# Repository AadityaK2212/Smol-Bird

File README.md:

# Smol-Bird
It is a mini console that can run a flappy bird game using a coin cell battery and a 8X8 LED grid. i originally saw someone make a small buisness card that can play video games, so I elaborated off of that and made it to only play flappy bird. also created one for pong. It runs on an ATtiny 1616 Microcontroller. I made this because it seemed like something fun, that I could just keep on me in case I ever got bored, and it would be cool to show off. I also need these for a competition at my school Hack Club, and i am giving these away as some of the prizes. It aslo seemed like a begginer friendly project that I learned more from.

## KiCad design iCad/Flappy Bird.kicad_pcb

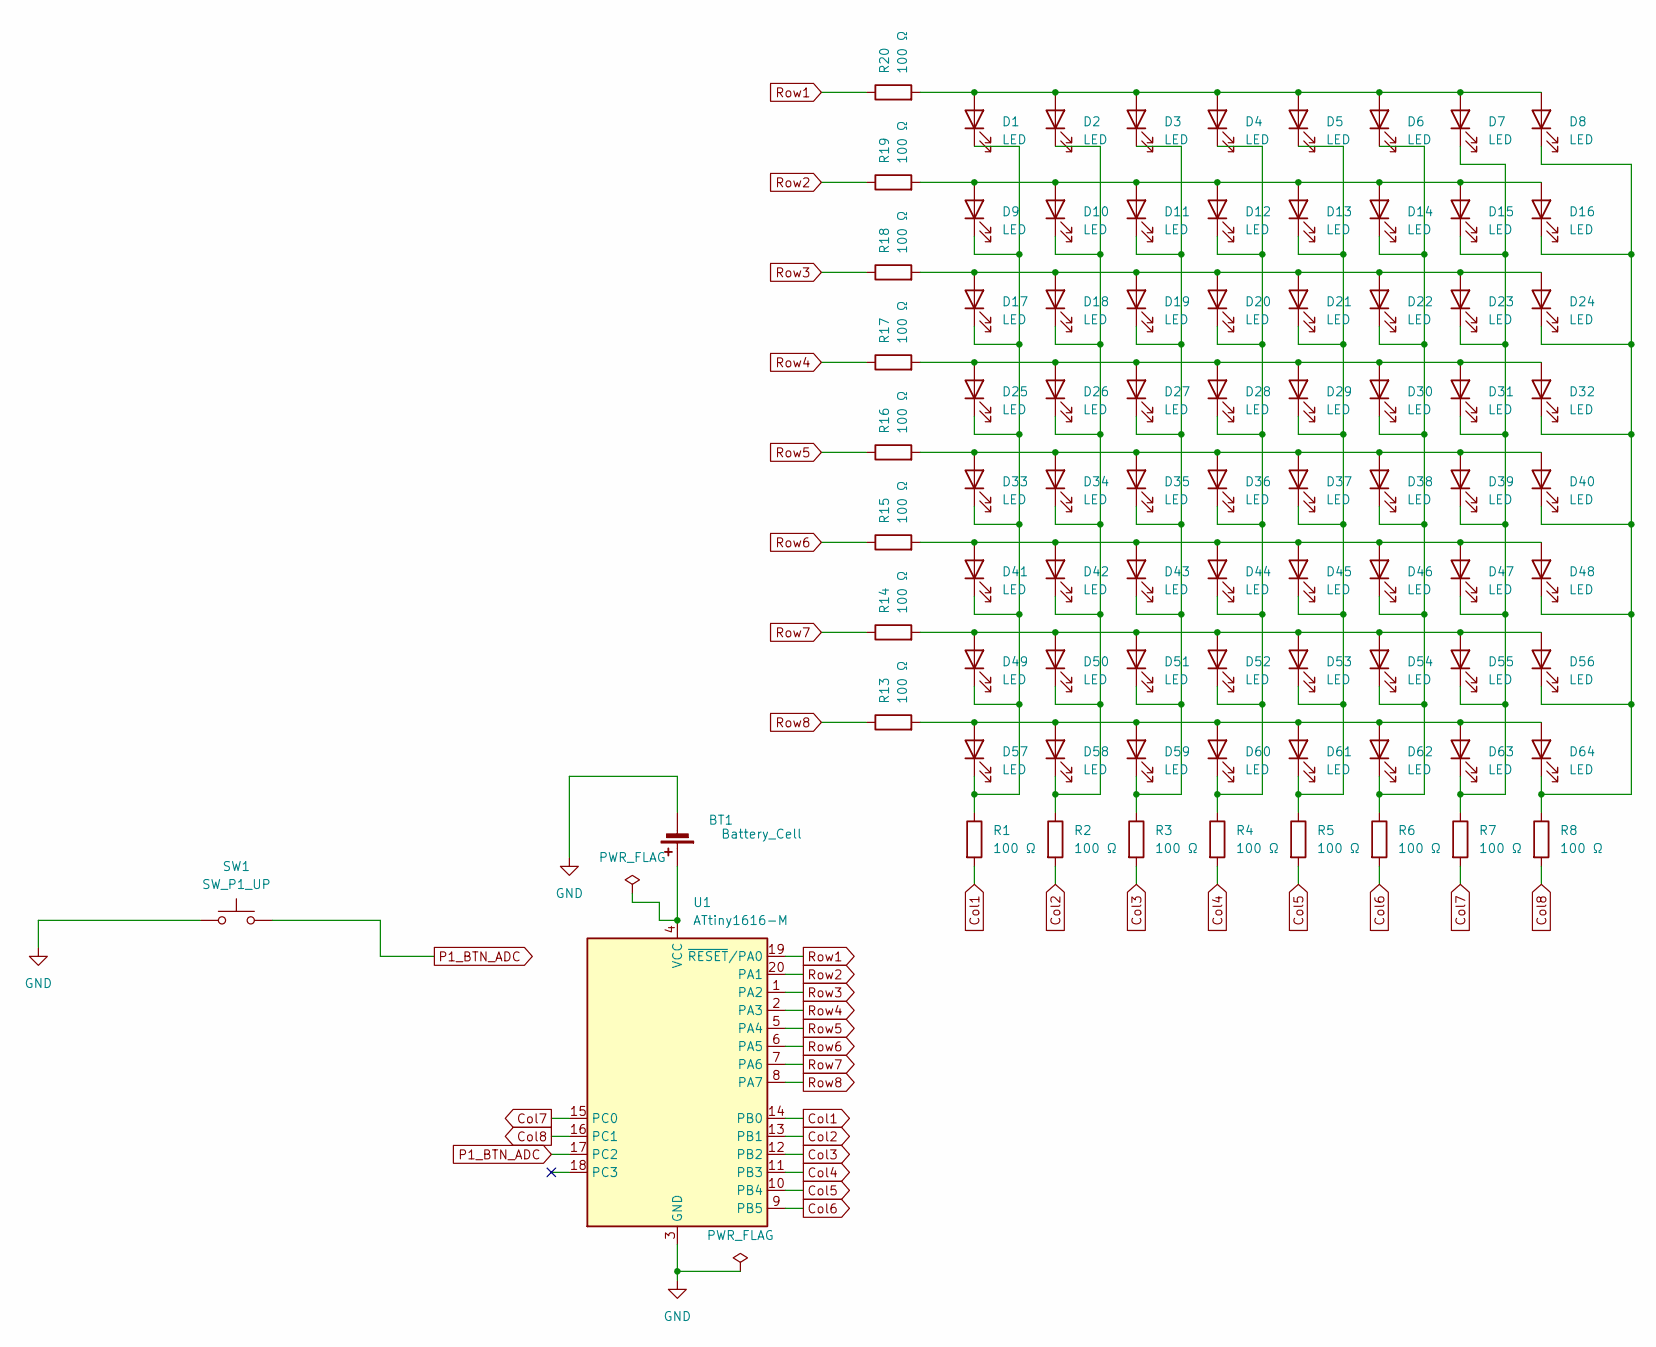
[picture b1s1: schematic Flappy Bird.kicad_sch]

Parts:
BT1: Battery_Cell; BatteryHolder_Keystone_1057_1x2032
D1, D2, D3, D4, D5, D6, D7, D8, D9, D10, D11, D12, D13, D14, D15, D16, D17, D18, D19, D20, D21, D22, D23, D24, D25, D26, D27, D28, D29, D30, D31, D32, D33, D34, D35, D36, D37, D38, D39, D40, D41, D42, D43, D44, D45, D46, D47, D48, D49, D50, D51, D52, D53, D54, D55, D56, D57, D58, D59, D60, D61, D62, D63, D64: LED; LED_0603_1608Metric
R1, R2, R3, R4, R5, R6, R7, R8, R13, R14, R15, R16, R17, R18, R19, R20: 100 Ω; R_0603_1608Metric
SW1: SW_P1_UP; SW_SPST_TL3342
U1: ATtiny1616-M; VQFN-20-1EP_3x3mm_P0.4mm_EP1.7x1.7mm

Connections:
Col1: R1.2, U1.14 (PB0)
Col2: R2.2, U1.13 (PB1)
Col3: R3.2, U1.12 (PB2)
Col4: R4.2, U1.11 (PB3)
Col5: R5.2, U1.10 (PB4)
Col6: R6.2, U1.9 (PB5)
Col7: R7.2, U1.15 (PC0)
Col8: R8.2, U1.16 (PC1)
GND: BT1.2 (-), SW1.1, U1.3 (GND), U1.21 (GND)
unnamed: BT1.1 (+), U1.4 (VCC)
unnamed: D1.2 (A), D2.2 (A), D3.2 (A), D4.2 (A), D5.2 (A), D6.2 (A), D7.2 (A), D8.2 (A), R20.2
unnamed: D1.1 (K), D9.1 (K), D17.1 (K), D25.1 (K), D33.1 (K), D41.1 (K), D49.1 (K), D57.1 (K), R1.1
unnamed: D9.2 (A), D10.2 (A), D11.2 (A), D12.2 (A), D13.2 (A), D14.2 (A), D15.2 (A), D16.2 (A), R19.2
unnamed: D2.1 (K), D10.1 (K), D18.1 (K), D26.1 (K), D34.1 (K), D42.1 (K), D50.1 (K), D58.1 (K), R2.1
unnamed: D3.1 (K), D11.1 (K), D19.1 (K), D27.1 (K), D35.1 (K), D43.1 (K), D51.1 (K), D59.1 (K), R3.1
unnamed: D4.1 (K), D12.1 (K), D20.1 (K), D28.1 (K), D36.1 (K), D44.1 (K), D52.1 (K), D60.1 (K), R4.1
unnamed: D5.1 (K), D13.1 (K), D21.1 (K), D29.1 (K), D37.1 (K), D45.1 (K), D53.1 (K), D61.1 (K), R5.1
unnamed: D6.1 (K), D14.1 (K), D22.1 (K), D30.1 (K), D38.1 (K), D46.1 (K), D54.1 (K), D62.1 (K), R6.1
unnamed: D7.1 (K), D15.1 (K), D23.1 (K), D31.1 (K), D39.1 (K), D47.1 (K), D55.1 (K), D63.1 (K), R7.1
unnamed: D8.1 (K), D16.1 (K), D24.1 (K), D32.1 (K), D40.1 (K), D48.1 (K), D56.1 (K), D64.1 (K), R8.1
unnamed: D17.2 (A), D18.2 (A), D19.2 (A), D20.2 (A), D21.2 (A), D22.2 (A), D23.2 (A), D24.2 (A), R18.2
unnamed: D25.2 (A), D26.2 (A), D27.2 (A), D28.2 (A), D29.2 (A), D30.2 (A), D31.2 (A), D32.2 (A), R17.2
unnamed: D33.2 (A), D34.2 (A), D35.2 (A), D36.2 (A), D37.2 (A), D38.2 (A), D39.2 (A), D40.2 (A), R16.2
unnamed: D41.2 (A), D42.2 (A), D43.2 (A), D44.2 (A), D45.2 (A), D46.2 (A), D47.2 (A), D48.2 (A), R15.2
unnamed: D49.2 (A), D50.2 (A), D51.2 (A), D52.2 (A), D53.2 (A), D54.2 (A), D55.2 (A), D56.2 (A), R14.2
unnamed: D57.2 (A), D58.2 (A), D59.2 (A), D60.2 (A), D61.2 (A), D62.2 (A), D63.2 (A), D64.2 (A), R13.2
P1_BTN_ADC: SW1.2, U1.17 (PC2)
Row1: R20.1, U1.19 (~RESET/PA0)
Row2: R19.1, U1.20 (PA1)
Row3: R18.1, U1.1 (PA2)
Row4: R17.1, U1.2 (PA3)
Row5: R16.1, U1.5 (PA4)
Row6: R15.1, U1.6 (PA5)
Row7: R14.1, U1.7 (PA6)
Row8: R13.1, U1.8 (PA7)

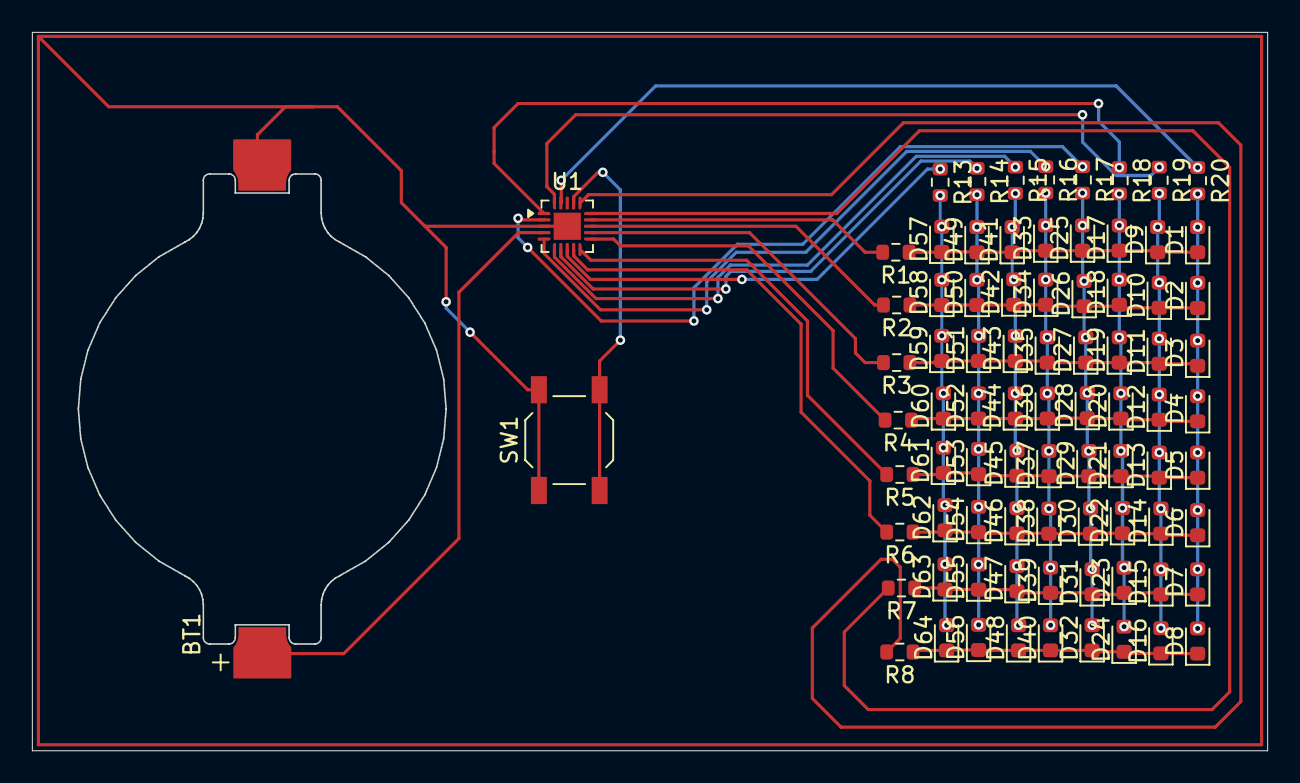
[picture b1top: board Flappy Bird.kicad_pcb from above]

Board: 2 copper layers, 77.2 x 44.9 mm, 83 parts (0 on the bottom side), 35 nets.

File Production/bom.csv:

Designator,Footprint,Quantity,Value,LCSC Part #
BT1,BatteryHolder_Keystone_1057_1x2032,1,Battery_Cell,USB Adapter,
"D1, D10, D11, D12, D13, D14, D15, D16, D17, D18, D19, D2, D20, D21, D22, D23, D24, D25, D26, D27, D28, D29, D3, D30, D31, D32, D33, D34, D35, D36, D37, D38, D39, D4, D40, D41, D42, D43, D44, D45, D46, D47, D48, D49, D5, D50, D51, D52, D53, D54, D55, D56, D57, D58, D59, D6, D60, D61, D62, D63, D64, D7, D8, D9",0603,64,LED, USB
"R1, R13, R14, R15, R16, R17, R18, R19, R2, R20, R3, R4, R5, R6, R7, R8",0603,16,100 Ω, N/A
SW1,SW_SPST_TL3342,1,SW_P1_UP,N/A
U1,VQFN-20-1EP_3x3mm_P0.4mm_EP1.7x1.7mm,1,ATtiny1616-M,https://www.amazon.com/gp/product/B0DNQ3SBXK/ref=ox_sc_act_t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

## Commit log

2026-05-06 Create TM
2026-05-06 Create TMP
2026-05-06 Enhance README with images and project details
    Added images and improved project description.
2026-05-06 Add more screenshots to README
    Added additional screenshots to showcase the project.
2026-05-10 Enhance README with project motivation and competition info
    Expanded project description to include motivation and competition details.
2026-05-13 Modify bom.csv with new component details
    Updated component values and added missing LCSC part numbers.
2026-05-13 Modify BOM entries and add USB component
    Updated the BOM to include a new USB entry and corrected formatting.
